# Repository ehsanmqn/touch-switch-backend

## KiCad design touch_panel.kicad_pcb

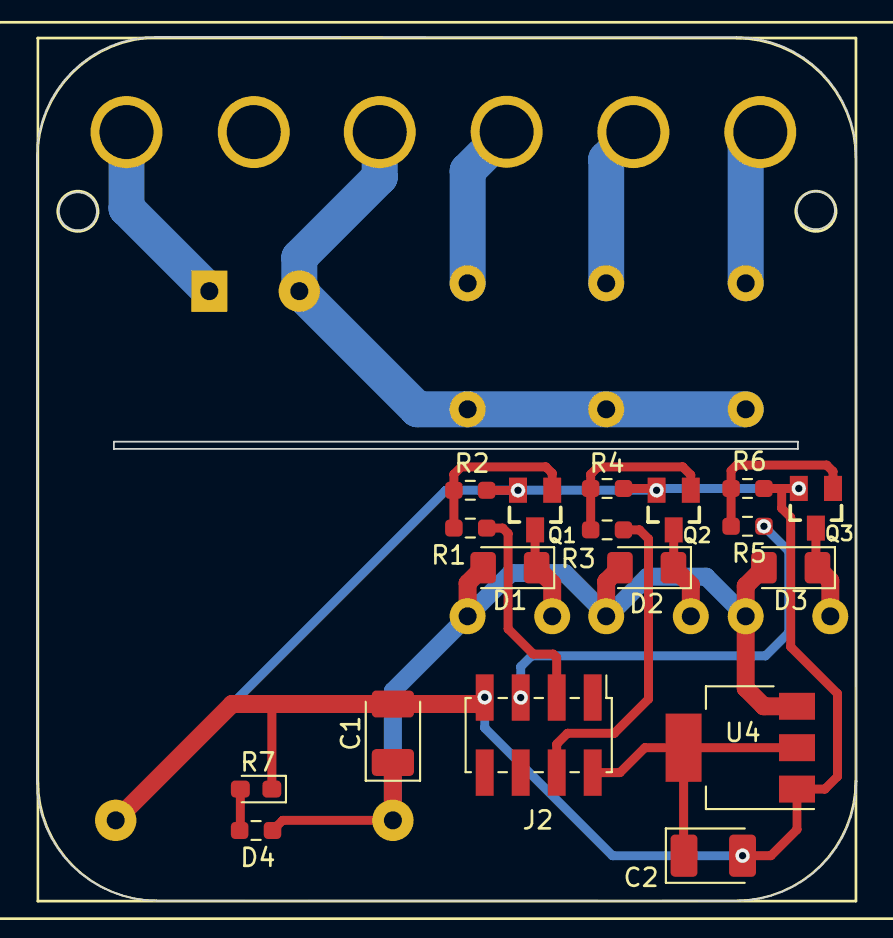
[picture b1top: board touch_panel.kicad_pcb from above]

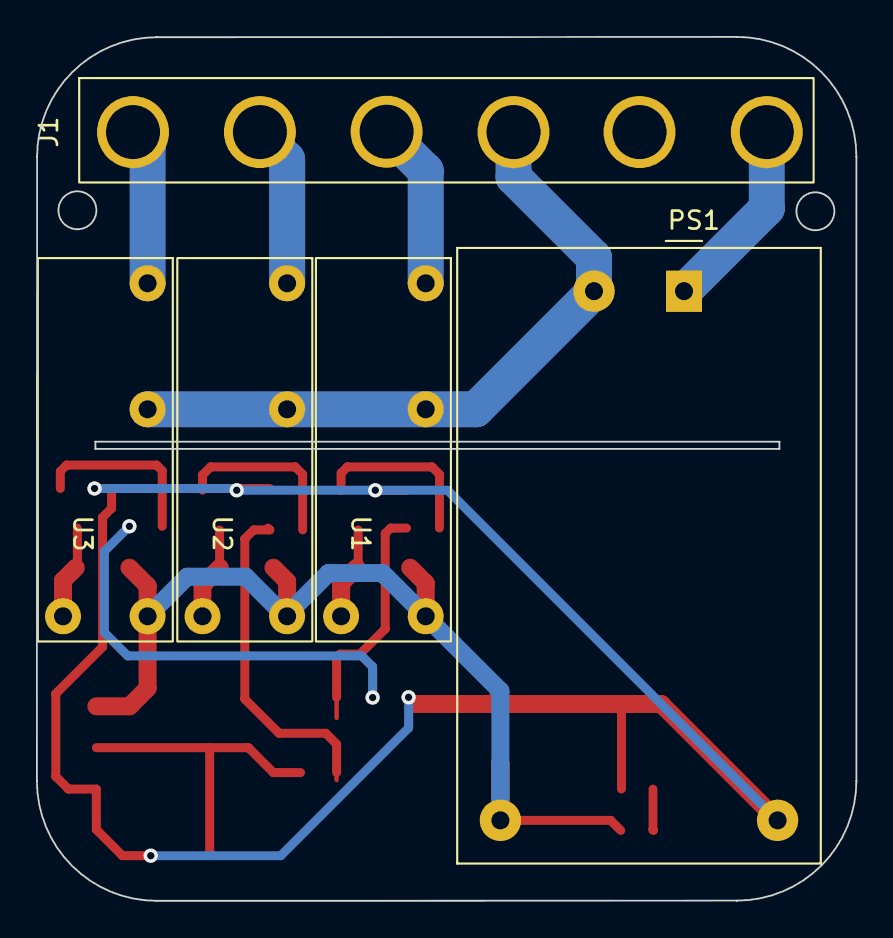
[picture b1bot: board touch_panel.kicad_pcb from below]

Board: 2 copper layers, 45.5 x 48.0 mm, 23 parts (2 on the bottom side), 18 nets.

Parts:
C1, C2: 22uF; CP_EIA-3528-12_Kemet-T_Pad1.50x2.35mm_HandSolder
D1, D2, D3: DIODE; D_1206_3216Metric_Pad1.42x1.75mm_HandSolder
D4: RED; LED_0603_1608Metric_Pad1.05x0.95mm_HandSolder
J1: Screw_Terminal_01x06; touch-relay
J2: 2x4 SMD 2.0 MM; PinHeader_2x04_P2.00mm_Vertical_SMD
PS1: HLK-PM01; Converter_ACDC_HiLink_HLK-PMxx
Q1, Q2, Q3: MMBT2222*; SOT23-BEC
R1, R3, R5: 1K; R_0603_1608Metric_Pad0.98x0.95mm_HandSolder
R2, R4, R6: 10K; R_0603_1608Metric_Pad0.98x0.95mm_HandSolder
R7: 2K; R_0603_1608Metric_Pad0.98x0.95mm_HandSolder
U1, U2, U3: c0942
U4: AMS1117-3.3; SOT-223-3_TabPin2

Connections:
+3V3: C2.1, J2.1 (Pin_2), U4.2 (VO)
+5V: C1.1, D1.2 (K), D2.2 (K), D3.2 (K), PS1.4 (+Vout), R7.2, U1.3, U2.3, U3.3, U4.3 (VI)
GND: C1.2, C2.2, D4.1 (K), J2.8 (Pin_7), PS1.3 (-Vout), Q1.E, Q2.E, Q3.E, R2.1, R4.1, R6.1, U4.1 (GND)
Load 1: J1.4, U1.1
Load 2: J1.5, U2.1
Load 3: J1.6, U3.1
unnamed: D1.1 (A), Q1.C, U1.4
unnamed: D2.1 (A), Q2.C, U2.4
unnamed: D3.1 (A), Q3.C, U3.4
unnamed: D4.2 (A), R7.1
unnamed: Q1.B, R1.1, R2.2
unnamed: Q2.B, R3.1, R4.2
unnamed: Q3.B, R5.1, R6.2
Neutral: J1.2, PS1.1 (AC/L)
Phase: J1.3, PS1.2 (AC/N), U1.2, U2.2, U3.2
Relay 1: J2.4 (Pin_3), R1.2
Relay 2: J2.3 (Pin_4), R3.2
Relay 3: J2.6 (Pin_5), R5.2

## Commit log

2022-03-19 Board finalized for printing
2022-04-03 nor changes performed# modified: HLK-PM01/HLK-PM01.step
